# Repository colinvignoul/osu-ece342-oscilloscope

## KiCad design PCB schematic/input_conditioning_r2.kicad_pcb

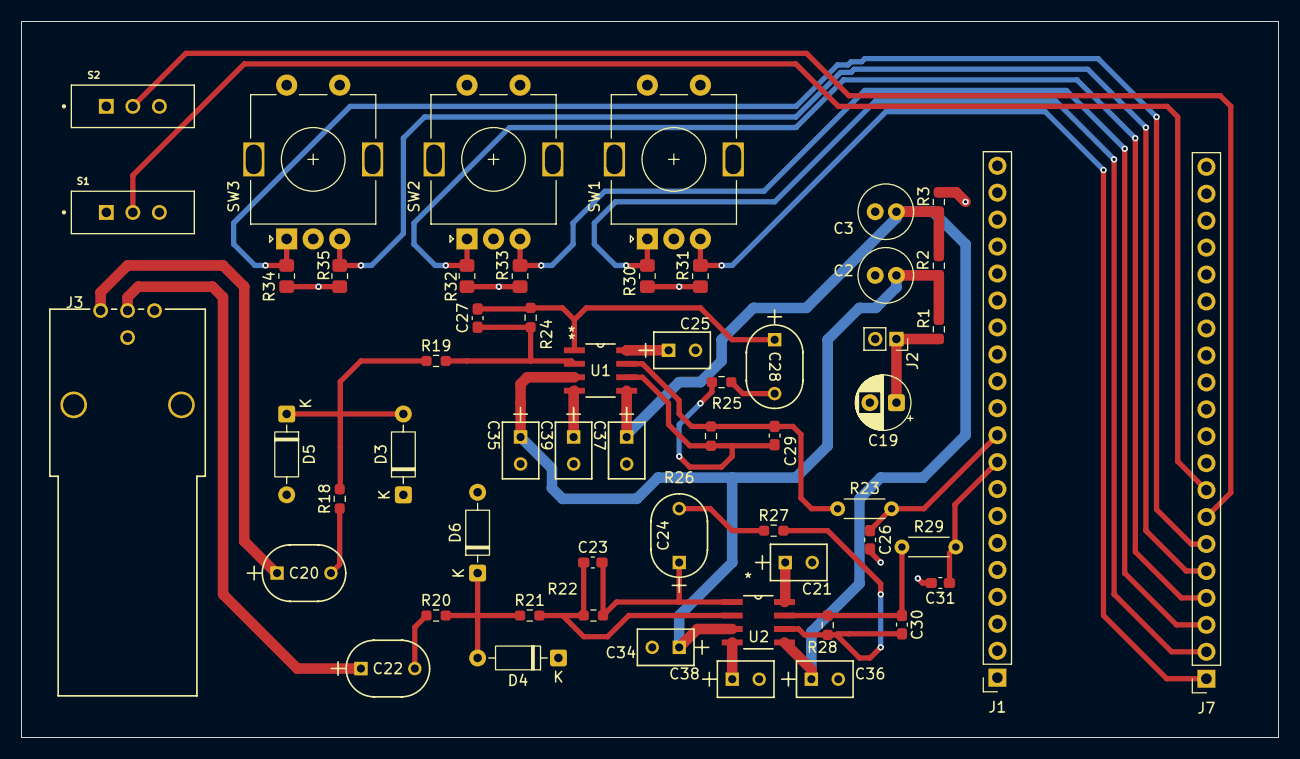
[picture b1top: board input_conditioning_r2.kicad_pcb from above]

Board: 4 copper layers, 118.5 x 67.5 mm, 57 parts (0 on the bottom side), 31 nets.

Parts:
C2, C3: 1u; C_Radial_D5.0mm_H11.0mm_P2.00mm
C19: 10u; CP_Radial_D5.0mm_P2.50mm
C20, C22, C24, C28: 1u; CAP_C330_KEM
C21, C25, C34, C35, C36, C37, C38, C39: 100n; CAP_AR20_AVX
C23, C27: 20p; C_0603_1608Metric_Pad1.08x0.95mm_HandSolder
C26, C31: 680p; C_0603_1608Metric_Pad1.08x0.95mm_HandSolder
C29, C30: 33p; C_0603_1608Metric_Pad1.08x0.95mm_HandSolder
D3, D4, D5, D6: 1N4148; D_DO-35_SOD27_P7.62mm_Horizontal
J1: Conn_01x10_Socket; PinSocket_1x20_P2.54mm_Vertical
J2: Conn_01x02_Socket; PinSocket_1x02_P2.00mm_Vertical
J3: Conn_Coaxial_x2; CONN_6575_AMP
J7: Conn_01x08_Socket; PinSocket_1x20_P2.54mm_Vertical
R1, R22, R24, R25, R27: 100k; R_0603_1608Metric_Pad0.98x0.95mm_HandSolder
R2, R3: 50k; R_0603_1608Metric_Pad0.98x0.95mm_HandSolder
R18, R19, R20, R21, R26, R28: 47k; R_0603_1608Metric_Pad0.98x0.95mm_HandSolder
R23, R29: 100; R_Axial_DIN0204_L3.6mm_D1.6mm_P5.08mm_Horizontal
R30, R31, R32, R33, R34, R35: 5k; R_0805_2012Metric_Pad1.20x1.40mm_HandSolder
S1, S2: MINI-SPDT-SW; SW_MINI-SPDT-SW
SW1: Shifting; RotaryEncoder_Alps_EC11E-Switch_Vertical_H20mm
SW2: Scaling; RotaryEncoder_Alps_EC11E-Switch_Vertical_H20mm
SW3: Trigger; RotaryEncoder_Alps_EC11E-Switch_Vertical_H20mm
U1, U2: OPA2365AID; D8

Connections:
+2V5: C2.1, C34.1, C35.1, R1.2, R2.1, U1.3 (INA+), U2.3 (INA+)
+3V3: J1.5, R30.1, R31.1, R32.1, R33.1, R34.1, R35.1, S1.1, S2.1
+5V: C19.1, C21.1, C25.1, D3.1 (K), D4.1 (K), J1.2, J2.1, R1.1, U1.8 (V+), U2.8 (V+)
/+1V25: C3.1, C36.1, C37.1, R2.2, R3.1, U1.5 (INB+), U2.5 (INB+)
/Real Signal Processing 1/ac_coupled: D3.2 (A), D5.1 (K), R18.2, R19.1
/Real Signal Processing 1/s1_in: C27.1, R19.2, R24.1, U1.2 (INA-)
/Real Signal Processing 1/s1_out: C27.2, C28.1, R24.2, U1.1 (VOUTA)
/Real Signal Processing 1/s2_in: C29.2, R25.2, R26.2, U1.6 (INB-)
/Real Signal Processing 1/s2_out: C29.1, R23.1, R26.1, U1.7 (VOUTB)
/Real Signal Processing 2/ac_coupled: D4.2 (A), D6.1 (K), R20.2, R21.1
/Real Signal Processing 2/s1_in: C23.1, R21.2, R22.1, U2.2 (INA-)
/Real Signal Processing 2/s1_out: C23.2, C24.1, R22.2, U2.1 (VOUTA)
/Real Signal Processing 2/s2_in: C30.2, R27.2, R28.2, U2.6 (INB-)
/Real Signal Processing 2/s2_out: C30.1, R28.1, R29.1, U2.7 (VOUTB)
/input_1: C20.1, J3.1 (IN1)
/input_2: C22.1, J3.2 (IN2)
/output_1: C26.1, J1.10, R23.2
/output_2: C31.1, J1.9, R29.2
GND: C2.2, C3.2, C19.2, C21.2, C25.2, C26.2, C31.2, C34.2, C35.2, C36.2, C37.2, C38.1, C38.2, C39.1, C39.2, D5.2 (A), D6.2 (A), J1.3, J2.2, J3.3 (EXT), R3.2, S1.3, S2.3, SW1.C, SW2.C, SW3.C, U1.4 (V-), U2.4 (V-)
unnamed: C20.2, R18.1
unnamed: C22.2, R20.1
unnamed: C24.2, R27.1
unnamed: C28.2, R25.1
unnamed: J7.1, R31.2, SW1.B
unnamed: J7.2, R30.2, SW1.A
unnamed: J7.3, R33.2, SW2.B
unnamed: J7.4, R32.2, SW2.A
unnamed: J7.5, R35.2, SW3.B
unnamed: J7.6, R34.2, SW3.A
unnamed: J7.7, S2.2
unnamed: J7.8, S1.2

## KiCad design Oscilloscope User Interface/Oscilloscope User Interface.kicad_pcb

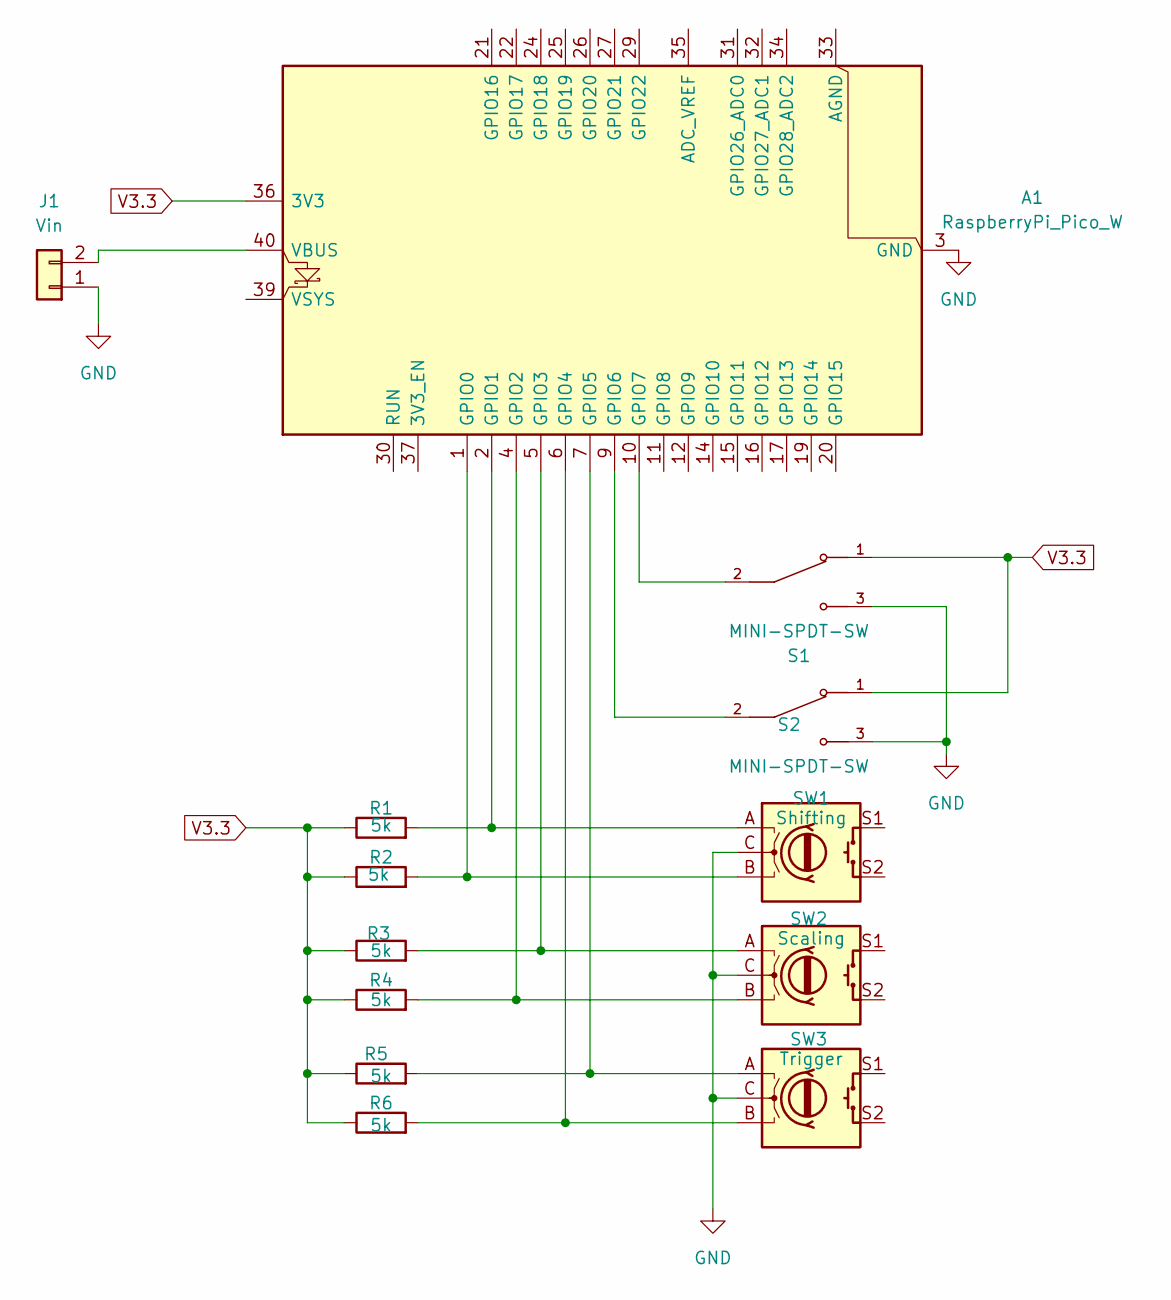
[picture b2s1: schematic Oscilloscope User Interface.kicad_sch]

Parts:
A1: RaspberryPi_Pico_W; RaspberryPi_Pico_W_SMD_HandSolder
J1: Vin; PinHeader_1x02_P2.54mm_Vertical
R1, R2, R3, R4, R5, R6: 5k; R_0201_0603Metric
S1, S2: MINI-SPDT-SW; SW_MINI-SPDT-SW
SW1: Shifting; RotaryEncoder_Alps_EC11E-Switch_Vertical_H20mm
SW2: Scaling; RotaryEncoder_Alps_EC12E-Switch_Vertical_H20mm
SW3: Trigger; RotaryEncoder_Alps_EC12E-Switch_Vertical_H20mm

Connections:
GND: A1.3 (GND), A1.8 (GND), A1.13 (GND), A1.18 (GND), A1.23 (GND), A1.28 (GND), A1.38 (GND), J1.1, S1.3, S2.3, SW1.C, SW2.C, SW3.C
unnamed: A1.1 (GPIO0), R2.2, SW1.B
unnamed: A1.2 (GPIO1), R1.2, SW1.A
unnamed: A1.4 (GPIO2), R4.2, SW2.B
unnamed: A1.5 (GPIO3), R3.2, SW2.A
unnamed: A1.6 (GPIO4), R6.2, SW3.B
unnamed: A1.7 (GPIO5), R5.2, SW3.A
unnamed: A1.9 (GPIO6), S2.2
unnamed: A1.10 (GPIO7), S1.2
unnamed: A1.40 (VBUS), J1.2
V3.3: A1.36 (3V3), R1.1, R2.1, R3.1, R4.1, R5.1, R6.1, S1.1, S2.1

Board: 2 copper layers, 13 parts (0 on the bottom side), 11 nets, no tracks yet.

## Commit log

2026-04-15 code file added
2026-04-19 Pseudocode stuff
2026-04-22 pseudocode
2026-04-24 VScode starting file
2026-04-24 "Start of UI"
2026-04-24 "Rename"
2026-04-24 "Added LED blinking to check if working"
2026-04-26 "Updated ui and started adc code with dma."
2026-04-27 Initial commit of current design for the signal processing block
2026-04-27 "Added trigger logic"
2026-04-27 Refactor and polishing
2026-04-27 added portable archive
2026-04-28 "Added some new files from the internet for working with dma"
2026-04-30 "Rotary library added"
2026-05-01 updated with available part sizes
2026-05-02 "Added UI schematic"
2026-05-02 "Updated UI schematic"
2026-05-04 "Deleted Main Code"
2026-05-04 schematic
2026-05-04 schematic layout mostly done
2026-05-05 "Updated UI part of PCB"
2026-05-05 oscilloscope ui PCB update
2026-05-06 pcb initial complete revision
2026-05-06 Fixed encoder footprints
2026-05-06 pcb fixed encoder footprints
2026-05-07 pcb almost ready to order
2026-05-07 pcb finished
2026-05-14 working on adc dma
2026-05-27 Rough C code to flash display between white and black as fast as possible
2026-05-27 Implement DMA to drive SPI and flash screen at perhaps yet higher a rate
2026-05-27 Rough demo of scaling, rendering samples from example array onto display
2026-05-27 Improve formatting, add todo
2026-05-27 "Idk small changes from just pulling up PCB schematic"
2026-05-29 "Updated UI for c++, added new project called osc_342, which should be the main project file now"
2026-05-30 "Finally got rotary encoder debouncing and interrupts working!"
2026-05-30 adc implementation hopefully ready and functional with usage example
2026-05-30 switched back to single buffer implementation
2026-05-31 Working code (I think?)
2026-05-31 Working code I think
2026-05-31 Update encoder and button behavior
2026-05-31 Update switch and encoder behavior
2026-05-31 added gitignore
2026-05-31 fixed gitignore
2026-05-31 Swap encoder behavior from vert/horz to shift/scale
2026-06-01 "Updated rotary encoeder transition table so clockwise is positive"
2026-06-01 Tidy up some code, make trigger channel indicator be purple
2026-06-02 Implement adaptive trigger noise reduction, interpolation at nominal timebases lower than 1
2026-06-02 Update encoder behavior
2026-06-03 Add run/hold switch on GP8
2026-06-03 Flip display orientation
